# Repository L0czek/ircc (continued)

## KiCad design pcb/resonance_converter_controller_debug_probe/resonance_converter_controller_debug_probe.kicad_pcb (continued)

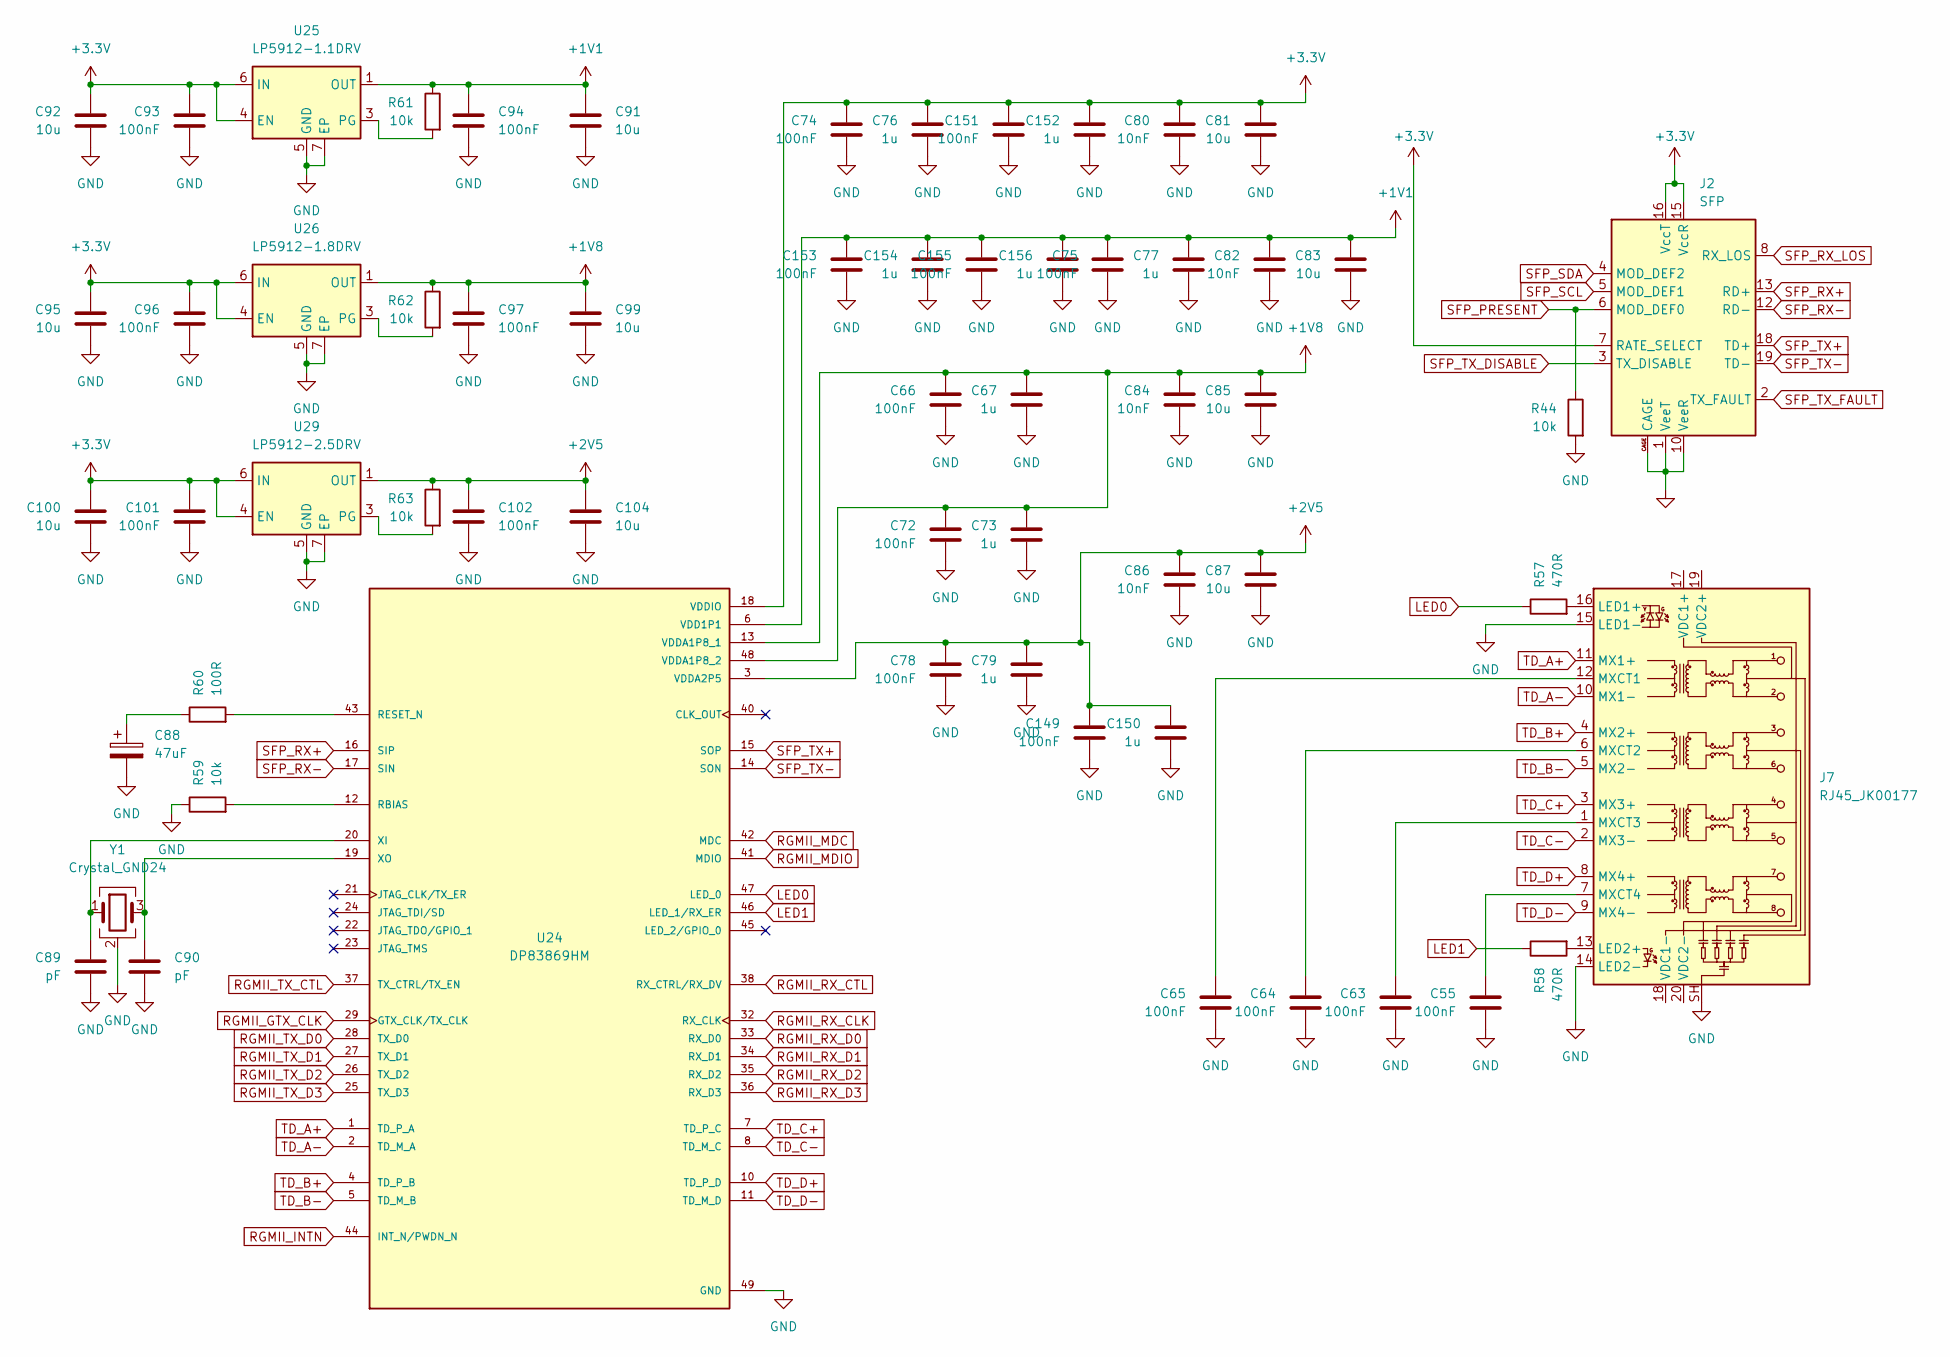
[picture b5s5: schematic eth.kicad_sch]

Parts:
C55, C63, C64, C65, C66, C72, C74, C75, C78, C93, C94, C96, C97, C101, C102, C149, C151, C153, C155: 100nF; C_0402_1005Metric
C67, C73, C76, C77, C79, C150, C152, C154, C156: 1u; C_0402_1005Metric
C80, C82, C84, C86: 10nF; C_0402_1005Metric
C81, C83, C85, C87, C91, C92, C95, C99, C100, C104: 10u; C_0805_2012Metric
C88: 47uF; C_1206_3216Metric
C89, C90: pF; C_0402_1005Metric
J2: SFP; Connector_SFP_and_Cage
J7: RJ45_JK00177; RJ45_Pulse_JK00177NL_Horizontal
R44, R59, R61, R62, R63: 10k; R_0402_1005Metric
R57, R58: 470R; R_0402_1005Metric
R60: 100R; R_0402_1005Metric
U24: DP83869HM; QFN50P700X700X100-49N; PARTREV A
U25: LP5912-1.1DRV; WSON-6-1EP_2x2mm_P0.65mm_EP1x1.6mm_ThermalVias
U26: LP5912-1.8DRV; WSON-6-1EP_2x2mm_P0.65mm_EP1x1.6mm_ThermalVias
U29: LP5912-2.5DRV; WSON-6-1EP_2x2mm_P0.65mm_EP1x1.6mm_ThermalVias
Y1: Crystal_GND24; Crystal_SMD_3225-4Pin_3.2x2.5mm

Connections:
+1V1: C75.1, C77.1, C82.1, C83.1, C91.1, C94.1, C153.1, C154.1, C155.1, C156.1, R61.1, U24.6 (VDD1P1), U24.31 (VDD1P1), U24.39 (VDD1P1), U25.1 (OUT)
+1V8: C66.1, C67.1, C72.1, C73.1, C84.1, C85.1, C97.1, C99.1, R62.1, U24.13 (VDDA1P8_1), U24.48 (VDDA1P8_2), U26.1 (OUT); also elsewhere on the board
+2V5: C78.1, C79.1, C86.1, C87.1, C102.1, C104.1, C149.1, C150.1, R63.1, U24.3 (VDDA2P5), U24.9 (VDDA2P5), U29.1 (OUT)
+3.3V: C74.1, C76.1, C80.1, C81.1, C92.1, C93.1, C95.1, C96.1, C100.1, C101.1, C151.1, C152.1, J2.7 (RATE_SELECT), J2.15 (VccR), J2.16 (VccT), U24.18 (VDDIO), U24.30 (VDDIO), U25.4 (EN), U25.6 (IN), U26.4 (EN), U26.6 (IN), U29.4 (EN), U29.6 (IN); also elsewhere on the board
GND: C55.2, C63.2, C64.2, C65.2, C66.2, C67.2, C72.2, C73.2, C74.2, C75.2, C76.2, C77.2, C78.2, C79.2, C80.2, C81.2, C82.2, C83.2, C84.2, C85.2, C86.2, C87.2, C88.2, C89.2, C90.2, C91.2, C92.2, C93.2, C94.2, C95.2, C96.2, C97.2, C99.2, C100.2, C101.2, C102.2, C104.2, C149.2, C150.2, C151.2, C152.2, C153.2, C154.2, C155.2, C156.2, J2.1 (VeeT), J2.9 (VeeR), J2.10 (VeeR), J2.11 (VeeR), J2.14 (VeeR), J2.17 (VeeT), J2.20 (VeeT), J2.CAGE, J7.14 (LED2-), J7.15 (LED1-), J7.SH, R44.2, R59.1, U24.49 (GND), U25.5 (GND), U25.7 (EP), U26.5 (GND), U26.7 (EP), U29.5 (GND), U29.7 (EP), Y1.2 (G), Y1.4 (G); also elsewhere on the board
LED0: R57.1, U24.47 (LED_0)
LED1: R58.1, U24.46 (LED_1/RX_ER)
unnamed: C88.1, R60.1
unnamed: J7.16 (LED1+), R57.2
unnamed: J7.13 (LED2+), R58.2
unnamed: C65.1, J7.12 (MXCT1)
unnamed: C64.1, J7.6 (MXCT2)
unnamed: C63.1, J7.1 (MXCT3)
unnamed: C55.1, J7.7 (MXCT4)
unnamed: R59.2, U24.12 (RBIAS)
unnamed: R60.2, U24.43 (RESET_N)
unnamed: C89.1, U24.20 (XI), Y1.1
unnamed: C90.1, U24.19 (XO), Y1.3
unnamed: R61.2, U25.3 (PG)
unnamed: R62.2, U26.3 (PG)
unnamed: R63.2, U29.3 (PG)
RGMII_GTX_CLK: U24.29 (GTX_CLK/TX_CLK); also elsewhere on the board
RGMII_INTN: U24.44 (INT_N/PWDN_N); also elsewhere on the board
RGMII_MDC: U24.42 (MDC); also elsewhere on the board
RGMII_MDIO: U24.41 (MDIO); also elsewhere on the board
RGMII_RX_CLK: U24.32 (RX_CLK); also elsewhere on the board
RGMII_RX_CTL: U24.38 (RX_CTRL/RX_DV); also elsewhere on the board
RGMII_RX_D0: U24.33 (RX_D0); also elsewhere on the board
RGMII_RX_D1: U24.34 (RX_D1); also elsewhere on the board
RGMII_RX_D2: U24.35 (RX_D2); also elsewhere on the board
RGMII_RX_D3: U24.36 (RX_D3); also elsewhere on the board
RGMII_TX_CTL: U24.37 (TX_CTRL/TX_EN); also elsewhere on the board
RGMII_TX_D0: U24.28 (TX_D0); also elsewhere on the board
RGMII_TX_D1: U24.27 (TX_D1); also elsewhere on the board
RGMII_TX_D2: U24.26 (TX_D2); also elsewhere on the board
RGMII_TX_D3: U24.25 (TX_D3); also elsewhere on the board
SFP_PRESENT: J2.6 (MOD_DEF0), R44.1
SFP_RX+: J2.13 (RD+), U24.16 (SIP)
SFP_RX-: J2.12 (RD-), U24.17 (SIN)
SFP_RX_LOS: J2.8 (RX_LOS)
SFP_SCL: J2.5 (MOD_DEF1); also elsewhere on the board
SFP_SDA: J2.4 (MOD_DEF2); also elsewhere on the board
SFP_TX+: J2.18 (TD+), U24.15 (SOP)
SFP_TX-: J2.19 (TD-), U24.14 (SON)
SFP_TX_DISABLE: J2.3 (TX_DISABLE)
SFP_TX_FAULT: J2.2 (TX_FAULT)
TD_A+: J7.11 (MX1+), U24.1 (TD_P_A)
TD_A-: J7.10 (MX1-), U24.2 (TD_M_A)
TD_B+: J7.4 (MX2+), U24.4 (TD_P_B)
TD_B-: J7.5 (MX2-), U24.5 (TD_M_B)
TD_C+: J7.3 (MX3+), U24.7 (TD_P_C)
TD_C-: J7.2 (MX3-), U24.8 (TD_M_C)
TD_D+: J7.8 (MX4+), U24.10 (TD_P_D)
TD_D-: J7.9 (MX4-), U24.11 (TD_M_D)

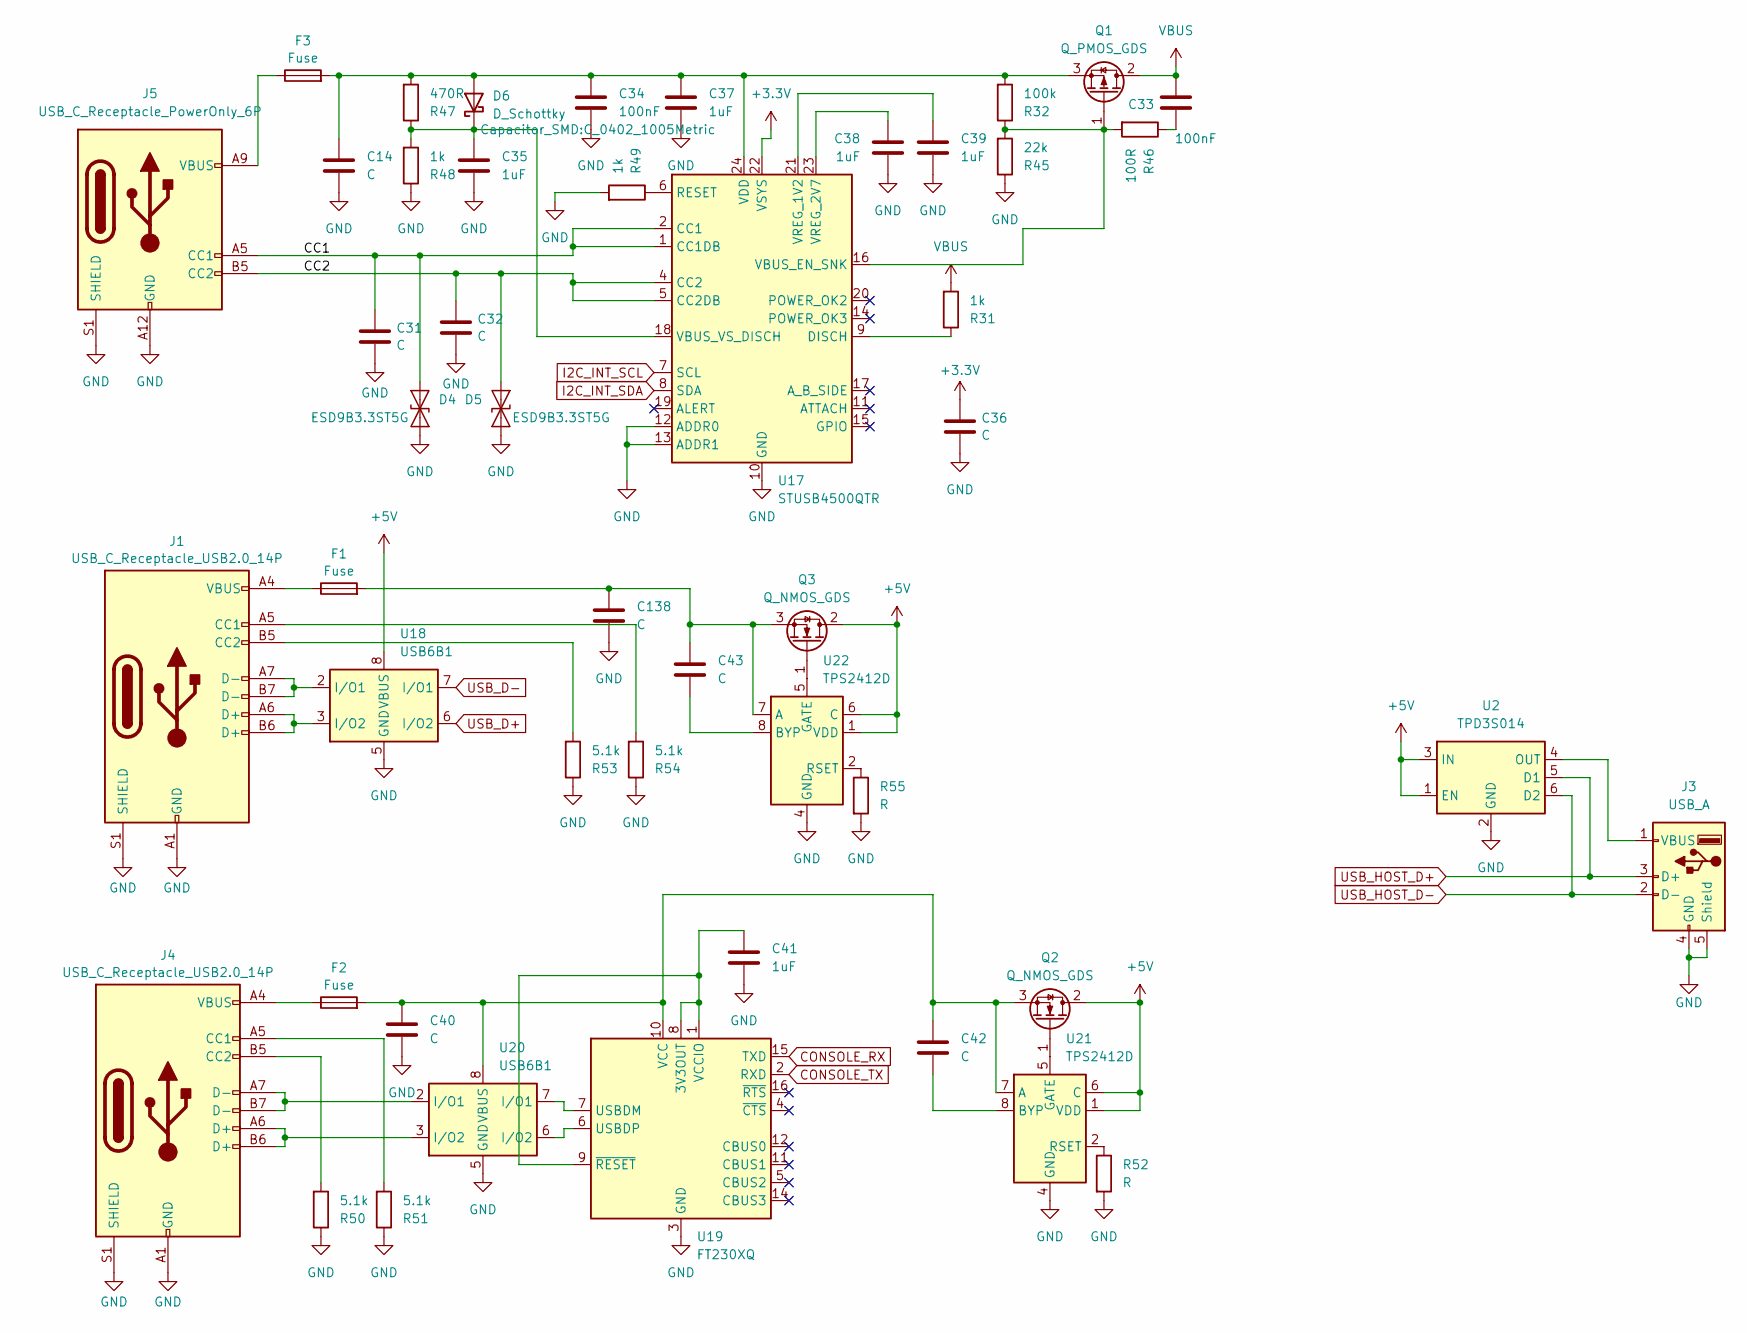
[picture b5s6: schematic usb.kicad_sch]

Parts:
C14, C40, C138: C; C_1206_3216Metric
C31, C32, C36: C; C_0402_1005Metric
C33: 100nF; C_0805_2012Metric
C34: 100nF; C_0402_1005Metric
C35, C37, C38, C39, C41: 1uF; C_0805_2012Metric
C42, C43: C; C_0805_2012Metric
D4, D5: ESD9B3.3ST5G; D_SOD-923
D6: D_Schottky; D_MiniMELF
F1, F2, F3: Fuse; Fuse_0805_2012Metric
J1, J4: USB_C_Receptacle_USB2.0_14P; USB_C_Receptacle_G-Switch_GT-USB-7010ASV
J3: USB_A; USB_A_Molex_67643_Horizontal
J5: USB_C_Receptacle_PowerOnly_6P; USB_C_Receptacle_GCT_USB4125-xx-x-0190_6P_TopMnt_Horizontal
Q1: Q_PMOS_GDS; TO-252-2
Q2, Q3: Q_NMOS_GDS; TO-252-2
R31, R48, R49: 1k; R_0402_1005Metric
R32: 100k; R_0402_1005Metric
R45: 22k; R_0402_1005Metric
R46: 100R; R_0402_1005Metric
R47: 470R; R_0402_1005Metric
R50, R51, R53, R54: 5.1k; R_0402_1005Metric
R52, R55: R; R_0402_1005Metric
U2: TPD3S014; SOT-23-6
U17: STUSB4500QTR; QFN-24-1EP_4x4mm_P0.5mm_EP2.7x2.7mm
U18, U20: USB6B1; SOIC-8_3.9x4.9mm_P1.27mm
U19: FT230XQ; QFN-16-1EP_4x4mm_P0.65mm_EP2.1x2.1mm
U21, U22: TPS2412D; TSSOP-8_4.4x3mm_P0.65mm

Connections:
+3.3V: C36.1, U17.22 (VSYS); also elsewhere on the board
+5V: Q2.2 (D), Q3.2 (D), U2.1 (EN), U2.3 (IN), U18.1 (VBUS), U18.8 (VBUS), U21.1 (VDD), U21.6 (C), U22.1 (VDD), U22.6 (C); also elsewhere on the board
/USB/CC1: C31.1, D4.2 (A2), J5.A5 (CC1), U17.1 (CC1DB), U17.2 (CC1)
/USB/CC2: C32.1, D5.2 (A2), J5.B5 (CC2), U17.4 (CC2), U17.5 (CC2DB)
CONSOLE_RX: U19.15 (TXD); also elsewhere on the board
CONSOLE_TX: U19.2 (RXD); also elsewhere on the board
GND: C14.2, C31.2, C32.2, C34.2, C35.2, C36.2, C37.2, C38.2, C39.2, C40.2, C41.2, C138.2, D4.1 (A1), D5.1 (A1), J1.A1 (GND), J1.A12 (GND), J1.B1 (GND), J1.B12 (GND), J1.S1 (SHIELD), J3.4 (GND), J3.5 (Shield), J4.A1 (GND), J4.A12 (GND), J4.B1 (GND), J4.B12 (GND), J4.S1 (SHIELD), J5.A12 (GND), J5.B12 (GND), J5.S1 (SHIELD), R45.1, R48.1, R49.2, R50.1, R51.1, R52.2, R53.1, R54.1, R55.2, U2.2 (GND), U17.10 (GND), U17.12 (ADDR0), U17.13 (ADDR1), U17.25 (GND), U18.4 (GND), U18.5 (GND), U19.3 (GND), U19.13 (GND), U19.17 (GND), U20.4 (GND), U20.5 (GND), U21.3 (GND), U21.4 (GND), U22.3 (GND), U22.4 (GND); also elsewhere on the board
I2C_INT_SCL: U17.7 (SCL); also elsewhere on the board
I2C_INT_SDA: U17.8 (SDA); also elsewhere on the board
unnamed: C33.2, R46.1
unnamed: C14.1, C34.1, C37.1, D6.2 (A), F3.2, Q1.3 (S), R32.2, R47.2, U17.24 (VDD)
unnamed: C35.1, D6.1 (K), R47.1, R48.2, U17.18 (VBUS_VS_DISCH)
unnamed: F1.1, J1.A4 (VBUS), J1.A9 (VBUS), J1.B4 (VBUS), J1.B9 (VBUS)
unnamed: F2.1, J4.A4 (VBUS), J4.A9 (VBUS), J4.B4 (VBUS), J4.B9 (VBUS)
unnamed: F3.1, J5.A9 (VBUS), J5.B9 (VBUS)
unnamed: J1.A5 (CC1), R54.2
unnamed: J1.B5 (CC2), R53.2
unnamed: J1.A6 (D+), J1.B6 (D+), U18.3 (I/O2)
unnamed: J1.A7 (D-), J1.B7 (D-), U18.2 (I/O1)
unnamed: J3.1 (VBUS), U2.4 (OUT)
unnamed: J4.A5 (CC1), R51.2
unnamed: J4.B5 (CC2), R50.2
unnamed: J4.A6 (D+), J4.B6 (D+), U20.3 (I/O2)
unnamed: J4.A7 (D-), J4.B7 (D-), U20.2 (I/O1)
unnamed: Q1.1 (G), R32.1, R45.2, R46.2, U17.16 (VBUS_EN_SNK)
unnamed: Q2.1 (G), U21.5 (GATE)
unnamed: C40.1, C42.1, F2.2, Q2.3 (S), U19.10 (VCC), U20.1 (VBUS), U20.8 (VBUS), U21.7 (A)
unnamed: Q3.1 (G), U22.5 (GATE)
unnamed: C43.1, C138.1, F1.2, Q3.3 (S), U22.7 (A)
unnamed: R31.1, U17.9 (DISCH)
unnamed: R49.1, U17.6 (RESET)
unnamed: C39.1, U17.21 (VREG_1V2)
unnamed: C38.1, U17.23 (VREG_2V7)
unnamed: C41.1, U19.1 (VCCIO), U19.8 (3V3OUT), U19.9 (~RESET)
unnamed: U19.7 (USBDM), U20.7 (I/O1)
unnamed: U19.6 (USBDP), U20.6 (I/O2)
unnamed: C42.2, U21.8 (BYP)
unnamed: R52.1, U21.2 (RSET)
unnamed: C43.2, U22.8 (BYP)
unnamed: R55.1, U22.2 (RSET)
USB_D+: U18.6 (I/O2); also elsewhere on the board
USB_D-: U18.7 (I/O1); also elsewhere on the board
USB_HOST_D+: J3.3 (D+), U2.5 (D1); also elsewhere on the board
USB_HOST_D-: J3.2 (D-), U2.6 (D2); also elsewhere on the board
VBUS: C33.1, Q1.2 (D), R31.2; also elsewhere on the board

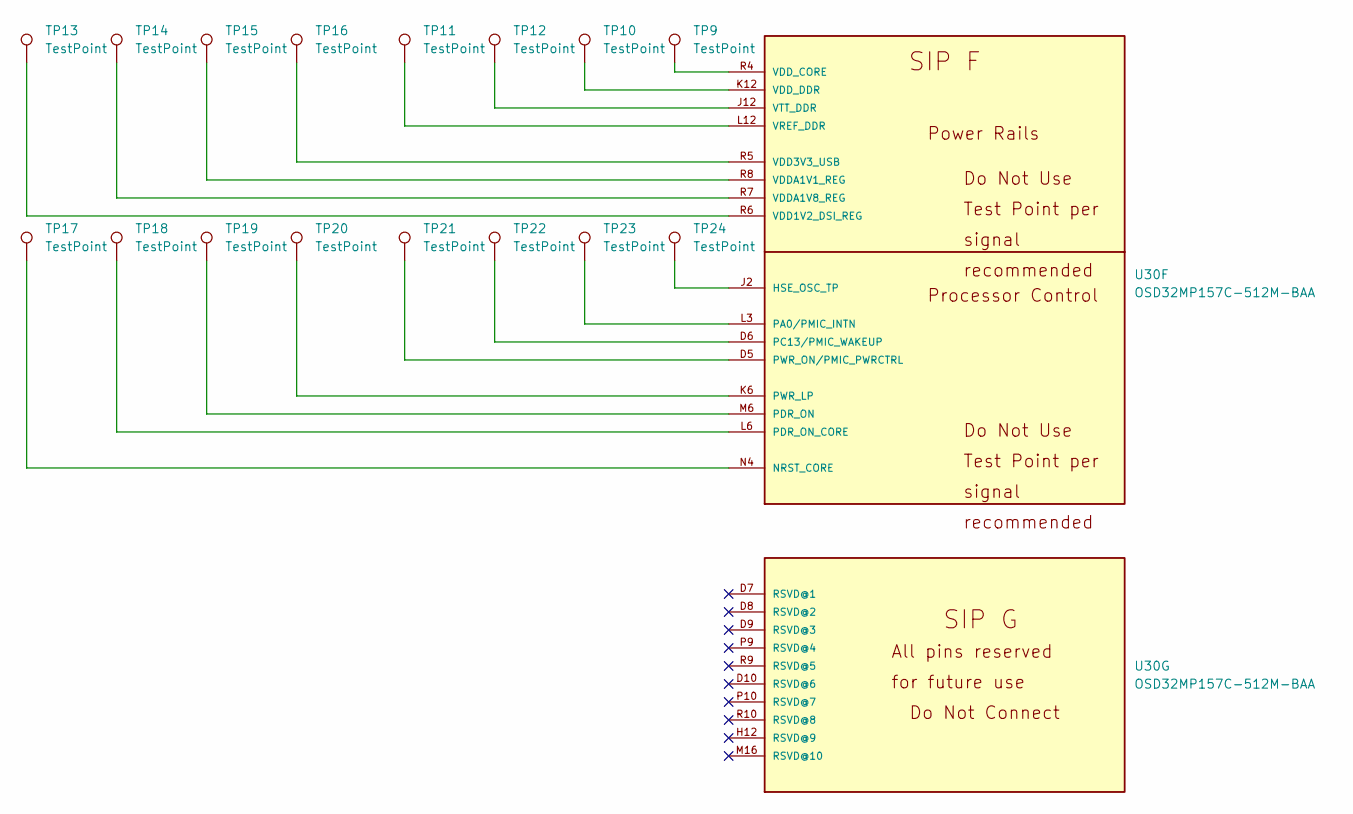
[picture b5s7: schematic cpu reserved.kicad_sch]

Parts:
TP9, TP10, TP11, TP12, TP13, TP14, TP15, TP16, TP17, TP18, TP19, TP20, TP21, TP22, TP23, TP24: TestPoint; TestPoint_Pad_D1.0mm
U30: OSD32MP157C-512M-BAA; OSD32MP15X-BGA-324

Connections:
unnamed: TP24.1, U30.J2 (HSE_OSC_TP)
unnamed: TP17.1, U30.N4 (NRST_CORE)
unnamed: TP23.1, U30.L3 (PA0/PMIC_INTN)
unnamed: TP22.1, U30.D6 (PC13/PMIC_WAKEUP)
unnamed: TP19.1, U30.M6 (PDR_ON)
unnamed: TP18.1, U30.L6 (PDR_ON_CORE)
unnamed: TP20.1, U30.K6 (PWR_LP)
unnamed: TP21.1, U30.D5 (PWR_ON/PMIC_PWRCTRL)
unnamed: TP13.1, U30.R6 (VDD1V2_DSI_REG)
unnamed: TP16.1, U30.R5 (VDD3V3_USB)
unnamed: TP15.1, U30.R8 (VDDA1V1_REG)
unnamed: TP14.1, U30.R7 (VDDA1V8_REG)
unnamed: TP9.1, U30.R4 (VDD_CORE)
unnamed: TP10.1, U30.K12 (VDD_DDR)
unnamed: TP11.1, U30.L12 (VREF_DDR)
unnamed: TP12.1, U30.J12 (VTT_DDR)

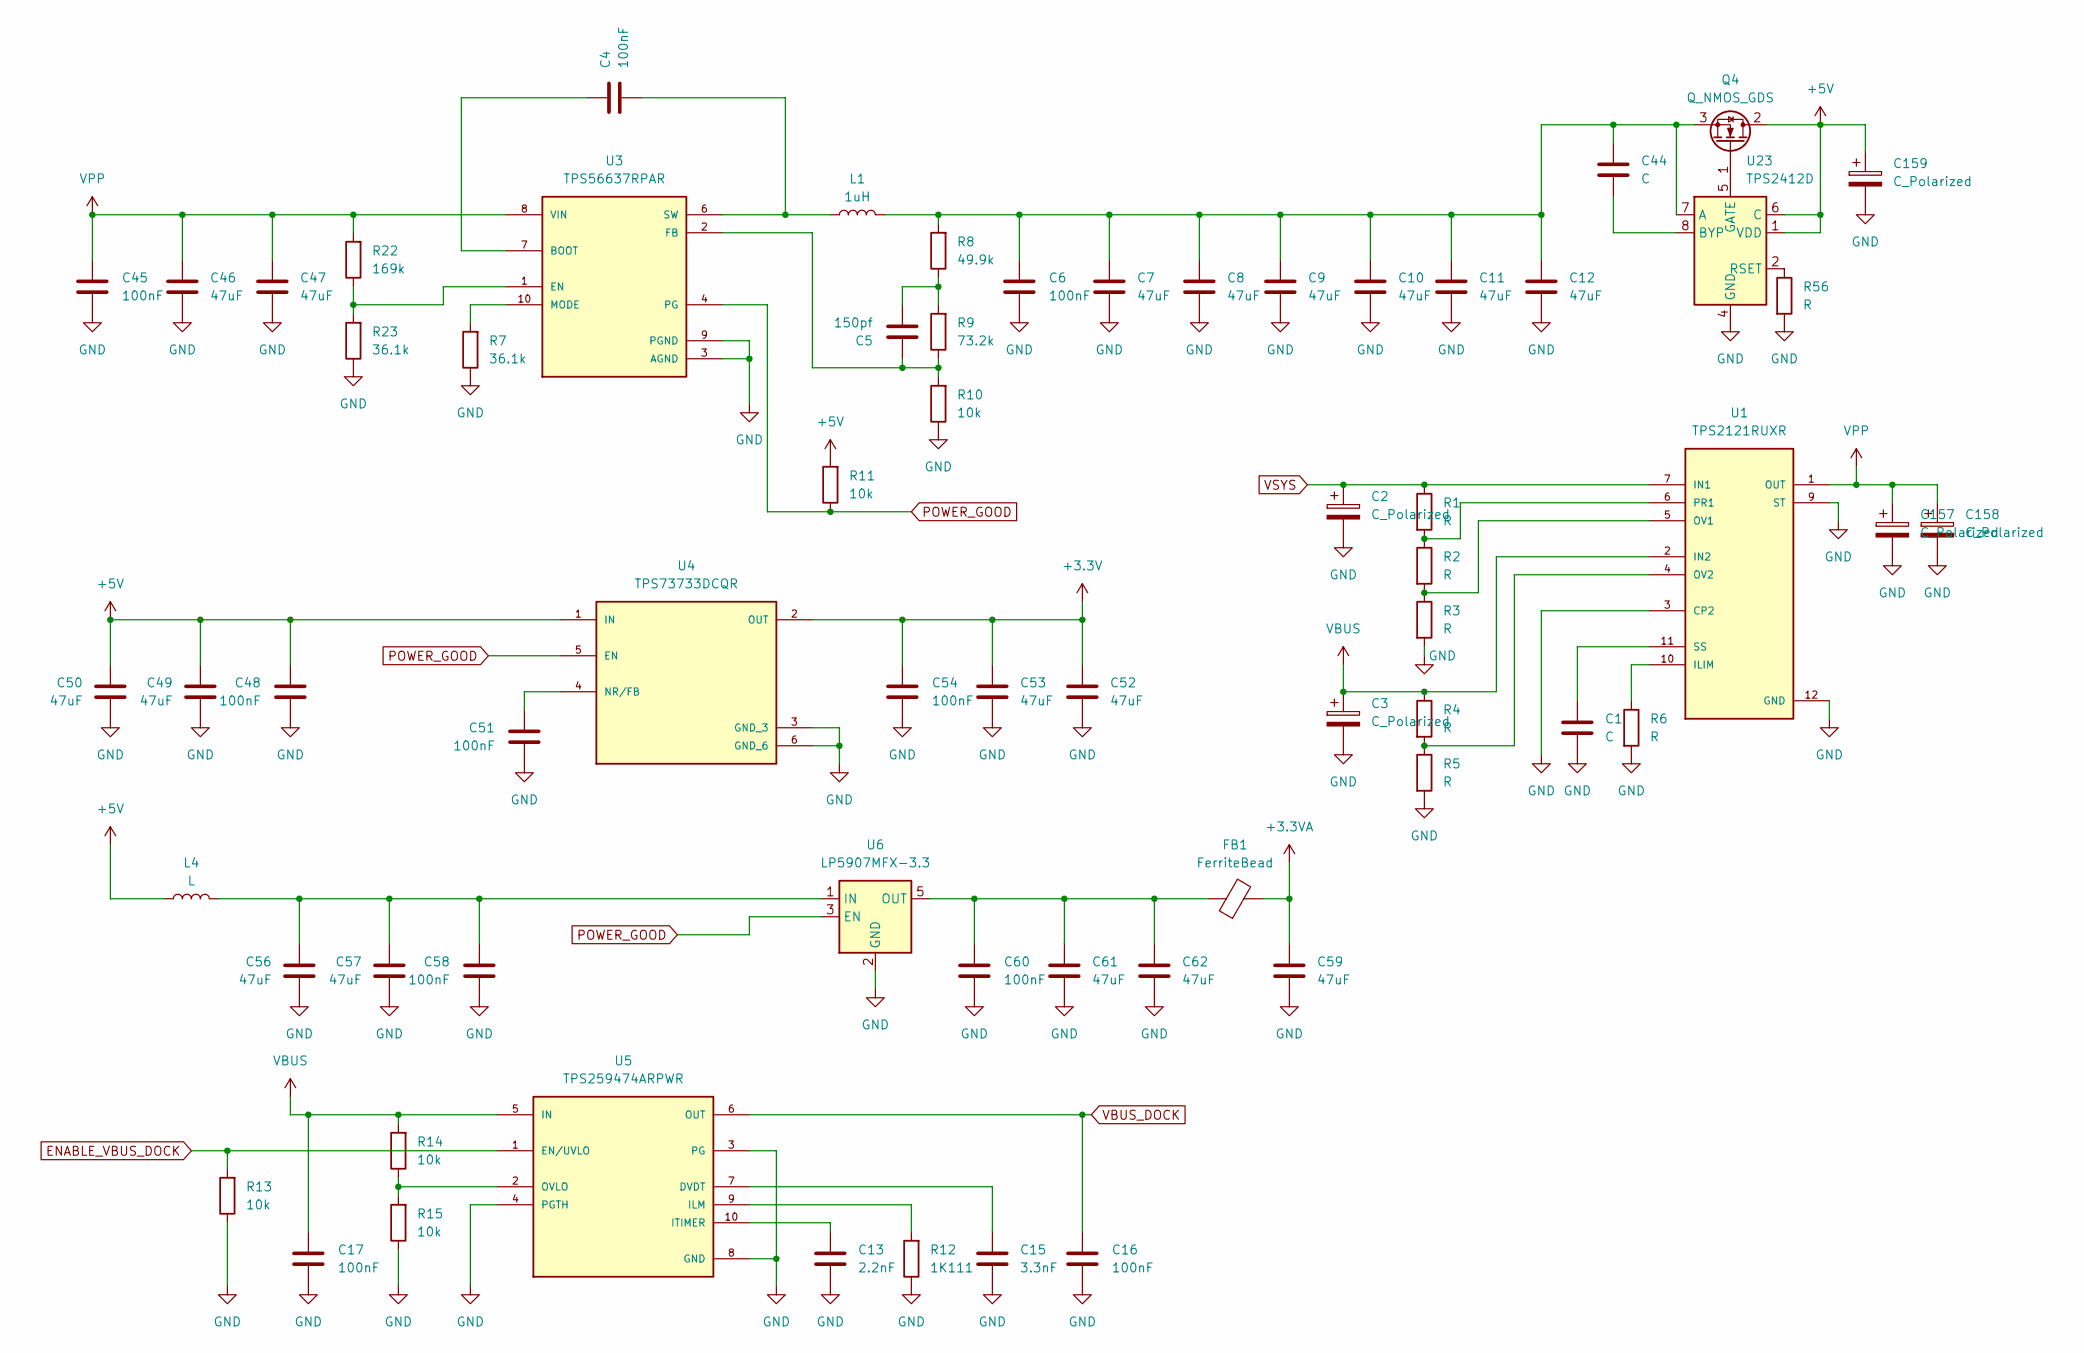
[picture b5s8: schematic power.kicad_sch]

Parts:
C1: C; C_0402_1005Metric
C2, C3, C157, C158, C159: C_Polarized; C_2220_5750Metric
C4, C6, C16, C17, C45, C48, C51, C54, C58, C60: 100nF; C_0402_1005Metric
C5: 150pf; C_0402_1005Metric
C7, C8, C9, C10, C11, C12, C46, C47, C49, C50, C52, C53, C56, C57, C59, C61, C62: 47uF; C_1206_3216Metric
C13: 2.2nF; C_0402_1005Metric
C15: 3.3nF; C_0402_1005Metric
C44: C; C_0805_2012Metric
FB1: FerriteBead; L_0805_2012Metric
L1: 1uH; L_10.4x10.4_H4.8
L4: L; L_1812_4532Metric
Q4: Q_NMOS_GDS; TO-252-2
R1, R2, R3, R4, R5, R6, R56: R; R_0402_1005Metric
R7, R23: 36.1k; R_0402_1005Metric
R8: 49.9k; R_0402_1005Metric
R9: 73.2k; R_0402_1005Metric
R10, R11, R13, R14, R15: 10k; R_0402_1005Metric
R12: 1K111; R_0402_1005Metric
R22: 169k; R_0402_1005Metric
U1: TPS2121RUXR; IC_TPS2121RUXR
U3: TPS56637RPAR; CONV_TPS56637RPAR; PARTREV A
U4: TPS73733DCQR; IC_TPS73733DCQR; PARTREV R
U5: TPS259474ARPWR; IC_TPS259474ARPWR; PARTREV A
U6: LP5907MFX-3.3; SOT-23-5
U23: TPS2412D; TSSOP-8_4.4x3mm_P0.65mm

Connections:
+3.3V: C52.1, C53.1, C54.1, U4.2 (OUT); also elsewhere on the board
+3.3VA: C59.1, FB1.2; also elsewhere on the board
+5V: C48.1, C49.1, C50.1, C159.1, L4.1, Q4.2 (D), R11.2, U4.1 (IN), U23.1 (VDD), U23.6 (C); also elsewhere on the board
ENABLE_VBUS_DOCK: R13.2, U5.1 (EN/UVLO)
GND: C1.2, C2.2, C3.2, C6.2, C7.2, C8.2, C9.2, C10.2, C11.2, C12.2, C13.2, C15.2, C16.2, C17.2, C45.2, C46.2, C47.2, C48.2, C49.2, C50.2, C51.2, C52.2, C53.2, C54.2, C56.2, C57.2, C58.2, C59.2, C60.2, C61.2, C62.2, C157.2, C158.2, C159.2, R3.2, R5.2, R6.2, R7.1, R10.1, R12.1, R13.1, R15.1, R23.1, R56.2, U1.3 (CP2), U1.9 (ST), U1.12 (GND), U3.3 (AGND), U3.9 (PGND), U4.3 (GND_3), U4.6 (GND_6), U5.3 (PG), U5.4 (PGTH), U5.8 (GND), U6.2 (GND), U23.3 (GND), U23.4 (GND); also elsewhere on the board
unnamed: C5.2, R8.1, R9.2
unnamed: Q4.1 (G), U23.5 (GATE)
unnamed: C6.1, C7.1, C8.1, C9.1, C10.1, C11.1, C12.1, C44.1, L1.2, Q4.3 (S), R8.2, U23.7 (A)
unnamed: R6.1, U1.10 (ILIM)
unnamed: R2.2, R3.1, U1.5 (OV1)
unnamed: R4.2, R5.1, U1.4 (OV2)
unnamed: R1.2, R2.1, U1.6 (PR1)
unnamed: C1.1, U1.11 (SS)
unnamed: C4.1, U3.7 (BOOT)
unnamed: R22.1, R23.2, U3.1 (EN)
unnamed: C5.1, R9.1, R10.2, U3.2 (FB)
unnamed: R7.2, U3.10 (MODE)
unnamed: C4.2, L1.1, U3.6 (SW)
unnamed: C51.1, U4.4 (NR/FB)
unnamed: C15.1, U5.7 (DVDT)
unnamed: R12.2, U5.9 (ILM)
unnamed: C13.1, U5.10 (ITIMER)
unnamed: R14.1, R15.2, U5.2 (OVLO)
unnamed: C56.1, C57.1, C58.1, L4.2, U6.1 (IN)
unnamed: C60.1, C61.1, C62.1, FB1.1, U6.5 (OUT)
unnamed: C44.2, U23.8 (BYP)
unnamed: R56.1, U23.2 (RSET)
POWER_GOOD: R11.1, U3.4 (PG), U4.5 (EN), U6.3 (EN)
VBUS: C3.1, C17.1, R4.1, R14.2, U1.2 (IN2), U1.2_1 (IN2), U5.5 (IN); also elsewhere on the board
VBUS_DOCK: C16.1, U5.6 (OUT); also elsewhere on the board
VPP: C45.1, C46.1, C47.1, C157.1, C158.1, R22.2, U1.1 (OUT), U1.1_1 (OUT), U1.8 (OUT), U1.8_1 (OUT), U3.8 (VIN)
VSYS: C2.1, R1.1, U1.7 (IN1), U1.7_1 (IN1); also elsewhere on the board

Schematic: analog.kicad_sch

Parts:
C30, C68, C69, C70, C71, C98, C103: 100nF; C_0402_1005Metric
D3, D7, D10, D11, D12, D13, D37: ESD9B3.3ST5G; D_SOD-923
R38, R43, R76, R78: 10K; R_0402_1005Metric
U9, U10, U11, U27: INA169; SOT-23-5
U12, U16: MCP4441-xxxx-ST; TSSOP-20_4.4x6.5mm_P0.65mm
U28: OPA356xxDBV; SOT-23-5

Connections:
+3.3V: C30.1, C103.1, U12.4 (HVC/A0), U12.15 (~RESET), U12.16 (A1), U12.17 (VDD), U16.4 (HVC/A0), U16.15 (~RESET), U16.16 (A1), U16.17 (VDD); also elsewhere on the board
+3.3VA: C68.2, C69.2, C70.2, C71.2, C98.1, U9.5 (V+), U10.5 (V+), U11.5 (V+), U27.5 (V+), U28.5 (V+); also elsewhere on the board
AUX_ADC: D3.2 (A2), R43.2; also elsewhere on the board
DAC_OUT: D37.2 (A2), R78.2; also elsewhere on the board
GND: C30.2, C68.1, C69.1, C70.1, C71.1, C98.2, C103.2, D3.1 (A1), D7.1 (A1), D10.1 (A1), D11.1 (A1), D12.1 (A1), D13.1 (A1), D37.1 (A1), R38.1, R43.1, R78.1, U9.2 (GND), U9.4 (-), U10.2 (GND), U10.4 (-), U11.2 (GND), U11.4 (-), U12.2 (P3W), U12.3 (P3B), U12.7 (VSS), U12.8 (P1B), U12.9 (P1W), U12.12 (P0W), U12.13 (P0B), U12.18 (P2B), U12.19 (P2W), U16.1 (P3A), U16.7 (VSS), U16.12 (P0W), U16.13 (P0B), U27.2 (GND), U27.4 (-), U28.2 (V-); also elsewhere on the board
I2C_INT_SCL: U12.5 (SCL), U16.5 (SCL); also elsewhere on the board
I2C_INT_SDA: U12.6 (SDA), U16.6 (SDA); also elsewhere on the board
ISENSE_1: D7.2 (A2), U9.3 (+); also elsewhere on the board
ISENSE_1_OUT: U9.1, U12.20 (P2A)
ISENSE_2: D10.2 (A2), U27.3 (+); also elsewhere on the board
ISENSE_2_OUT: U12.1 (P3A), U27.1
ISENSE_3: D11.2 (A2), U10.3 (+); also elsewhere on the board
ISENSE_3_OUT: U10.1, U12.10 (P1A)
ISENSE_4: D12.2 (A2), U11.3 (+); also elsewhere on the board
ISENSE_4_OUT: U11.1, U12.11 (P0A)
unnamed: R76.1, U16.11 (P0A), U28.4 (-)
VSENSE_IN: D13.2 (A2), R38.2, U28.3 (+); also elsewhere on the board
VSENSE_OUT: R76.2, U28.1

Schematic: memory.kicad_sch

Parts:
C105, C106, C108: 100nF; C_0402_1005Metric
C107: 10uF; C_1206_3216Metric
C109: 100uF; C_1206_3216Metric
J9, J10: Micro_SD_Card_Det2; microSD_HC_Hirose_DM3BT-DSF-PEJS
R67: 0R; R_0402_1005Metric; not fitted
R68: 240K; R_0402_1005Metric
R69: 100K; R_0402_1005Metric
U31: TPS2553DRVR; SON65P200X200X80-7N

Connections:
+3.3V: C105.1, R67.1, R69.2, U31.6 (IN); also elsewhere on the board
GND: C105.2, C106.2, C107.2, C108.2, C109.2, J9.6 (VSS), J9.10 (DET_A), J9.11 (SHIELD), J10.6 (VSS), J10.10 (DET_A), J10.11 (SHIELD), R68.2, U31.5 (GND), U31.7 (EP); also elsewhere on the board
unnamed: C107.1, C108.1, C109.1, J9.4 (VDD), J10.4 (VDD), U31.1 (OUT)
unnamed: C106.1, R69.1, U31.3 (~FAULT), U31.4 (EN)
unnamed: R67.2, R68.1, U31.2 (ILIM)
SD0_CLK: J9.5 (CLK); also elsewhere on the board
SD0_CMD: J9.3 (CMD); also elsewhere on the board
SD0_D0: J9.7 (DAT0); also elsewhere on the board
SD0_D1: J9.8 (DAT1); also elsewhere on the board
SD0_D2: J9.1 (DAT2); also elsewhere on the board
SD0_D3: J9.2 (DAT3/CD); also elsewhere on the board
SD0_DET: J9.9 (DET_B)
SD1_CLK: J10.5 (CLK); also elsewhere on the board
SD1_CMD: J10.3 (CMD); also elsewhere on the board
SD1_D0: J10.7 (DAT0); also elsewhere on the board
SD1_D1: J10.8 (DAT1); also elsewhere on the board
SD1_D2: J10.1 (DAT2); also elsewhere on the board
SD1_D3: J10.2 (DAT3/CD); also elsewhere on the board
SD1_DET: J10.9 (DET_B)

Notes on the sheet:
3.3 bus max 100mA

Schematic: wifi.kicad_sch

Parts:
C110: C_Polarized; CP_EIA-7343-31_Kemet-D
H1: MountingHole_Pad; screw-stud
J11: Bus_M.2_Socket_E; MDTXXXXXX001
R64, R65, R70: 10k; R_0402_1005Metric
R66, R71: 0R; R_0402_1005Metric; not fitted

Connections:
+1V8: R64.1, R65.1; also elsewhere on the board
+3.3V: C110.1, J11.2 (3.3V), J11.4 (3.3V), J11.72 (3.3V), J11.74 (3.3V), R70.1; also elsewhere on the board
BLE_ENABLE: J11.54 (~W_DISABLE2)
BLE_UART_CTS: J11.34 (UART_CTS); also elsewhere on the board
BLE_UART_RTS: J11.36 (UART_RTS); also elsewhere on the board
BLE_UART_RXD: J11.22 (UART_RXD); also elsewhere on the board
BLE_UART_TXD: J11.32 (UART_TXD); also elsewhere on the board
BLE_UART_WAKE: J11.20 (~UART_WAKE), R70.2, R71.2
GND: C110.2, H1.1 (1_1), J11.1 (GND), J11.7 (GND), J11.18 (GND), J11.33 (GND), J11.39 (GND), J11.45 (GND), J11.51 (GND), J11.57 (GND), J11.63 (GND), J11.69 (GND), J11.75 (GND), J11.S1 (GND), J11.S2 (GND); also elsewhere on the board
unnamed: J11.40 (VENDOR_DEFINED), R66.1
unnamed: J11.42 (VENDOR_DEFINED), R71.1
WIFI_ENABLE: J11.56 (~W_DISABLE1)
WIFI_SDIO_CLK: J11.9 (SDIO_CLK); also elsewhere on the board
WIFI_SDIO_CMD: J11.11 (SDIO_CMD); also elsewhere on the board
WIFI_SDIO_D0: J11.13 (SDIO_DATA0); also elsewhere on the board
WIFI_SDIO_D1: J11.15 (SDIO_DATA1); also elsewhere on the board
WIFI_SDIO_D2: J11.17 (SDIO_DATA2); also elsewhere on the board
WIFI_SDIO_D3: J11.19 (SDIO_DATA3); also elsewhere on the board
WIFI_SDIO_RESET: J11.23 (~SDIO_RESET), R65.2
WIFI_SDIO_WAKE: J11.21 (~SDIO_WAKE), R64.2, R66.2
WIFI_SUSCLK: J11.50 (SUSCLK)

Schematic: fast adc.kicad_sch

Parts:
C18, C19, C24, C25, C26, C27, C28, C29, C139, C140, C141, C143, C144: 100nF; C_0402_1005Metric
C20, C21, C22, C23: 10uF; C_1206_3216Metric
C142, C145, C146, C147, C148: 10u; C_0805_2012Metric
D1, D2: ESD9B3.3ST5G; D_SOD-923
L2: L; L_0805_2012Metric
R16, R17, R18, R19, R20, R21, R24, R25, R26, R29, R30, R33, R34, R35, R36, R37, R39, R40: 10K; R_0402_1005Metric
R27, R28, R41, R42: 10R; R_0402_1005Metric
R72: 10k; R_0402_1005Metric
U7: ADC3910D125IRSMT; IC_ADC3910D125IRSMT; PARTREV A
U8, U14: OPA333xxDBV; SOT-23-5
U13, U15: THS4541IRGTT; QFN50P300X300X100-17N
U16: MCP4441-xxxx-ST; TSSOP-20_4.4x6.5mm_P0.65mm
U33: LP5912-1.8DRV; WSON-6-1EP_2x2mm_P0.65mm_EP1x1.6mm_ThermalVias

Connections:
1V8A: C28.1, C29.1, C147.1, C148.1, L2.2, U7.12 (AVDD), U7.13 (AVDD)
+3.3V: C139.1, U7.27 (IOVDD); also elsewhere on the board
+3.3VA: C26.1, C27.1, C140.1, C141.1, C142.1, C143.1, R26.1, R30.1, U8.5 (V+), U13.5 (VS+-2), U13.6 (VS+-3), U13.7 (VS+), U13.8 (VS+-1), U13.12 (PDN), U14.5 (V+), U15.5 (VS+-2), U15.6 (VS+-3), U15.7 (VS+), U15.8 (VS+-1), U15.12 (PDN), U33.4 (EN), U33.6 (IN); also elsewhere on the board
ADC_ALERT: U7.20 (ALERT)
ADC_CLK: U7.8 (CLK)
ADC_D0: U7.4 (D0); also elsewhere on the board
ADC_D1: U7.3 (D1); also elsewhere on the board
ADC_D2: U7.2 (D2); also elsewhere on the board
ADC_D3: U7.1 (D3); also elsewhere on the board
ADC_D4: U7.32 (D4); also elsewhere on the board
ADC_D5: U7.31 (D5); also elsewhere on the board
ADC_D6: U7.26 (D6); also elsewhere on the board
ADC_D7: U7.25 (D7); also elsewhere on the board
ADC_D8: U7.24 (D8); also elsewhere on the board
ADC_D9: U7.23 (D9); also elsewhere on the board
ADC_D10: U7.22 (D10); also elsewhere on the board
ADC_D11: U7.21 (D11); also elsewhere on the board
ADC_DCLK: U7.30 (DCLK); also elsewhere on the board
ADC_OEN: U7.6 (~OEN/PD)
ADC_RESET: U7.9 (RESET)
ADC_SCLK: U7.18 (SCLK); also elsewhere on the board
ADC_SDIO: U7.19 (SDIO); also elsewhere on the board
ADC_SS: U7.16 (~SEN); also elsewhere on the board
GND: C18.1, C21.1, C22.1, C24.1, C26.2, C27.2, C28.2, C29.2, C139.2, C140.2, C141.2, C142.2, C143.2, C144.2, C145.2, C146.2, C147.2, C148.2, D1.1 (A1), D2.1 (A1), R24.1, R25.2, R29.1, R33.2, U7.17 (VREF), U7.28 (DGND), U7.33 (GND), U8.2 (V-), U13.13 (VS--2), U13.14 (VS--3), U13.15 (VS-), U13.16 (VS--1), U14.2 (V-), U15.13 (VS--2), U15.14 (VS--3), U15.15 (VS-), U15.16 (VS--1), U33.5 (GND), U33.7 (EP); also elsewhere on the board
unnamed: C18.2, R17.2
unnamed: C19.1, R18.2
unnamed: C19.2, R21.1, U8.1
unnamed: C20.1, R20.2
unnamed: C23.1, R34.2
unnamed: C24.2, R36.2
unnamed: C25.1, R37.2
unnamed: C25.2, R35.1, U14.1
unnamed: R28.1, U7.11 (INAM)
unnamed: R27.1, U7.10 (INAP)
unnamed: R42.1, U7.15 (INBM/NC)
unnamed: R41.1, U7.14 (INBP/NC)
unnamed: C21.2, R25.1, R26.2, U8.3 (+)
unnamed: R19.1, U13.4 (FB+)
unnamed: R16.1, U13.1 (FB-)
unnamed: R16.2, R17.1, U13.2 (IN+)
unnamed: R18.1, R19.2, U13.3 (IN-)
unnamed: R27.2, U13.10 (OUT+)
unnamed: R28.2, U13.11 (OUT-)
unnamed: C22.2, R30.2, R33.1, U14.3 (+)
unnamed: U14.4 (-), U16.19 (P2W)
unnamed: R40.1, U15.4 (FB+)
unnamed: R39.1, U15.1 (FB-)
unnamed: R36.1, R39.2, U15.2 (IN+)
unnamed: R37.1, R40.2, U15.3 (IN-)
unnamed: R41.2, U15.10 (OUT+)
unnamed: R42.2, U15.11 (OUT-)
unnamed: R20.1, U16.10 (P1A)
unnamed: R21.2, U16.8 (P1B)
unnamed: U8.4 (-), U16.9 (P1W)
unnamed: R34.1, U16.20 (P2A)
unnamed: R35.2, U16.18 (P2B)
unnamed: C144.1, C145.1, C146.1, L2.1, R72.1, U33.1 (OUT)
unnamed: R72.2, U33.3 (PG)
OCD2_IN: C23.2, D2.2 (A2), R29.2; also elsewhere on the board
OCD_IN: C20.2, D1.2 (A2), R24.2; also elsewhere on the board
VOCM: U7.7 (VCM), U13.9 (VOCM), U15.9 (VOCM)

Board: 4 copper layers, 310 parts (62 on the bottom side), 264 nets, no tracks yet.
